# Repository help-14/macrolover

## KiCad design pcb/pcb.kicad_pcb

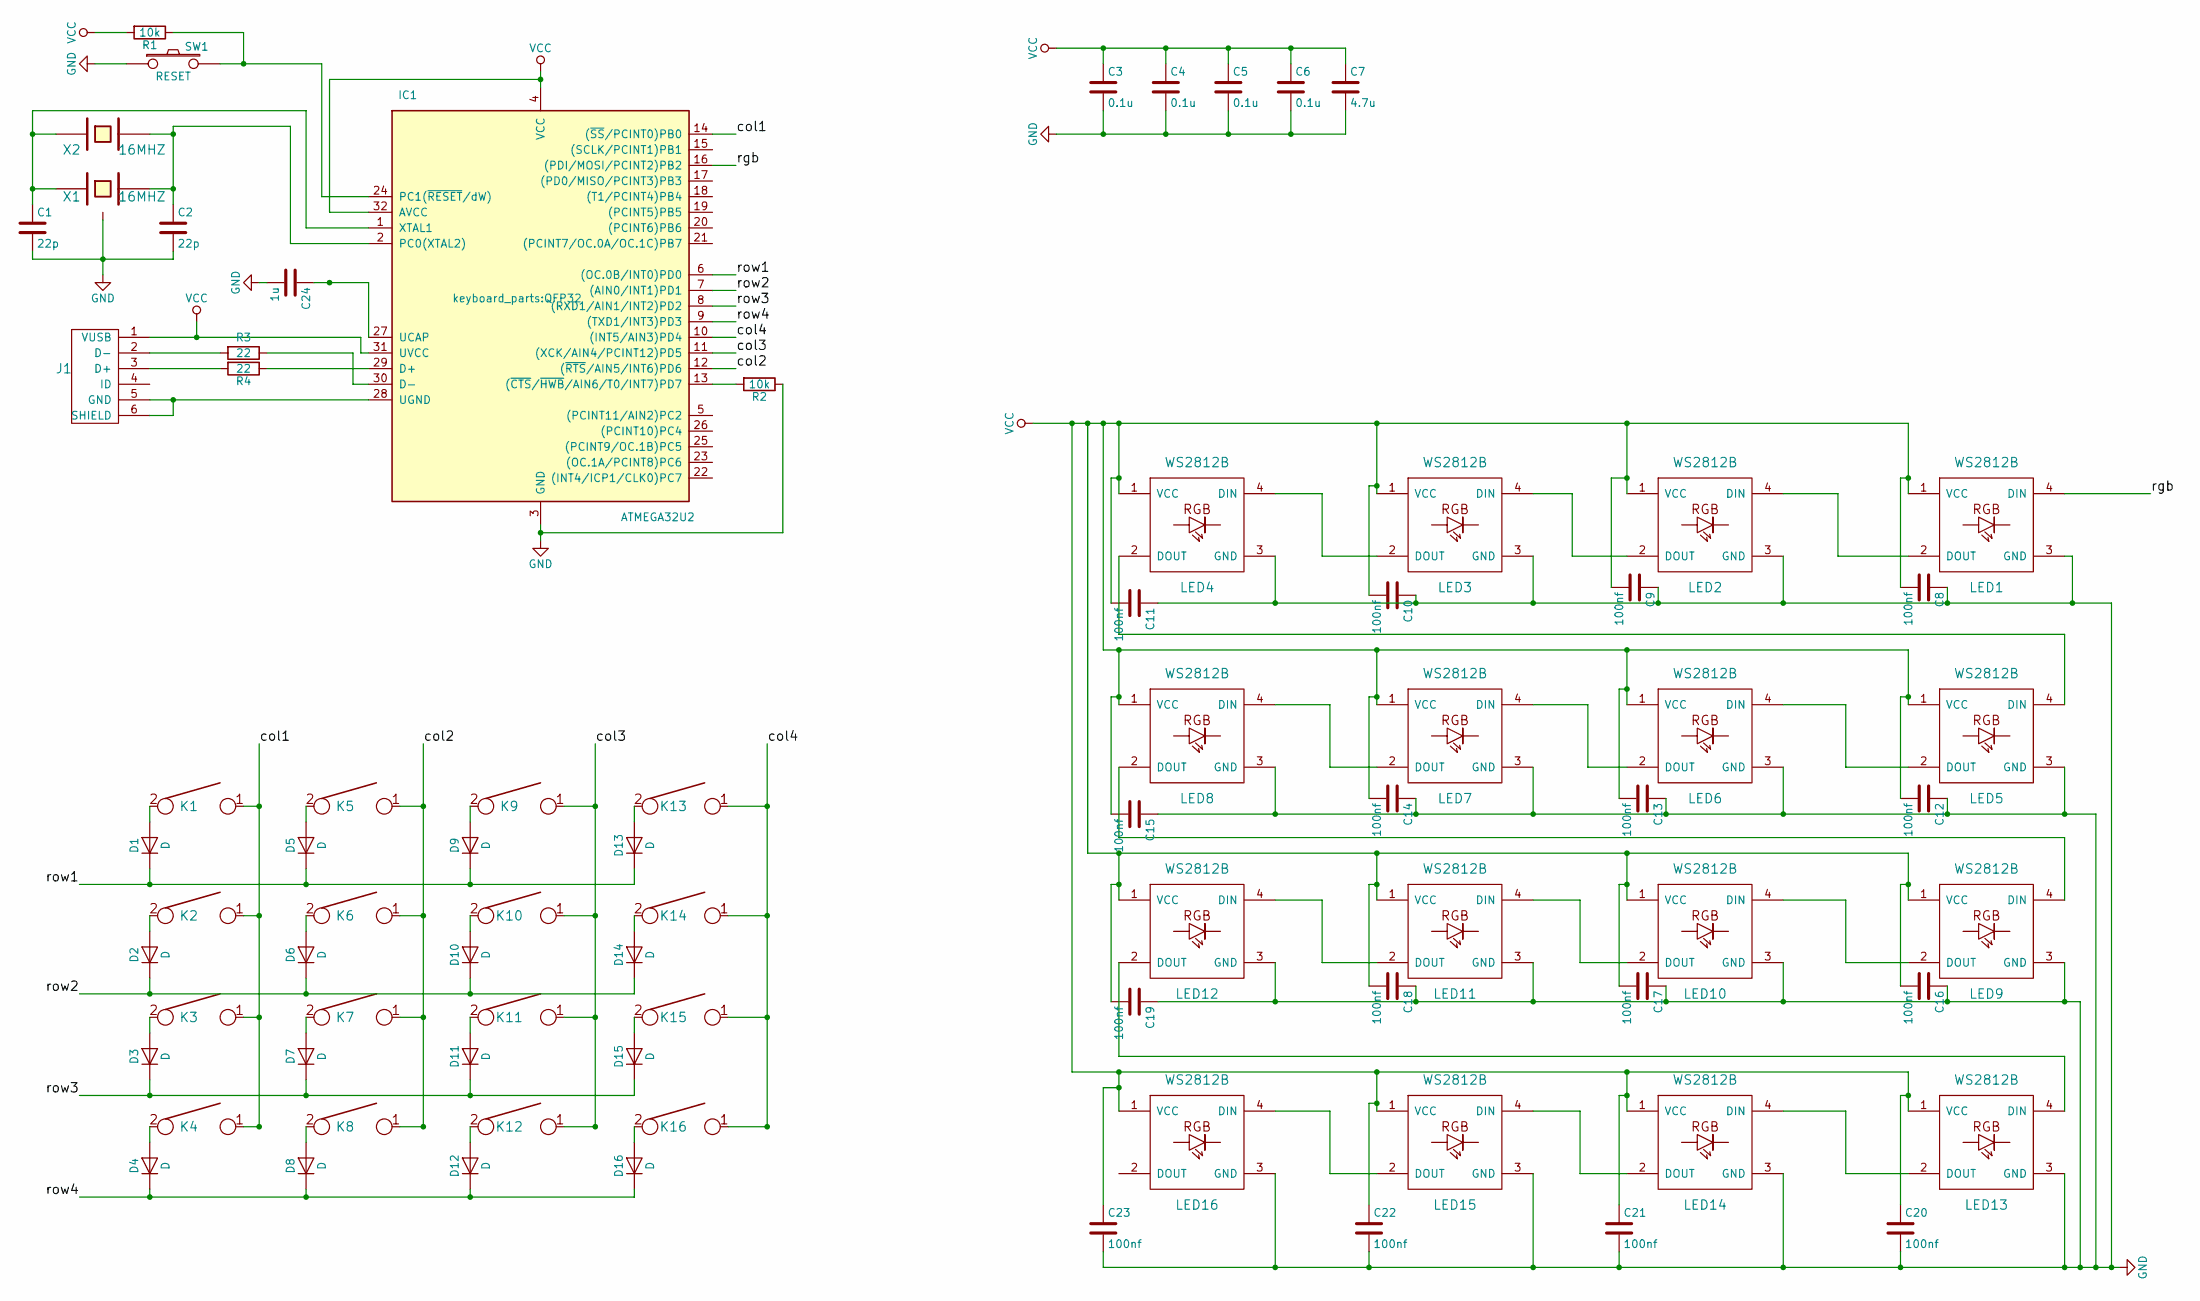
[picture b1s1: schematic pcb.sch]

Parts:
C1, C2: 22p; C_0805
C3, C4, C5, C6: 0.1u; C_0805
C7: 4.7u; C_0805
C8, C9, C10, C11, C12, C13, C14, C15, C16, C17, C18, C19, C20, C21, C22, C23: 100nf; C_0805
C24: 1u; C_0805
D1, D2, D3, D4, D5, D6, D7, D8, D9, D10, D11, D12, D13, D14, D15, D16: D; D_SOD123
IC1: ATMEGA32U2; QFP32
J1: USB_mini_B; USB_miniB_hirose_5S8
K1: 7; Mx_Alps_100
K2: 4; Mx_Alps_100
K3: 1; Mx_Alps_100
K4: 0; Mx_Alps_100
K5: 8; Mx_Alps_100
K6: 5; Mx_Alps_100
K7: 2; Mx_Alps_100
K8: DOT; Mx_Alps_100
K9: 9; Mx_Alps_100
K10: 6; Mx_Alps_100
K11: 3; Mx_Alps_100
K12: EQUAL; Mx_Alps_100
K13: DEVIDE; Mx_Alps_100
K14: *; Mx_Alps_100
K15: -; Mx_Alps_100
K16: +; Mx_Alps_100
LED1, LED2, LED3, LED4, LED5, LED6, LED7, LED8, LED9, LED10, LED11, LED12, LED13, LED14, LED15, LED16: WS2812B
R1, R2: 10k; R_0805
R3, R4: 22; R_0805
SW1: RESET; SW_SPST_TL3342
X1: 16MHZ; Crystal_SMD_SeikoEpson_TSX3225-4pin_3.2x2.5mm
X2: 16MHZ; XTAL_HC_49_TH

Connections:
/col1: IC1.14 ((~SS~/PCINT0)PB0), K1.1, K2.1, K3.1, K4.1
/col2: IC1.12 ((~RTS~/AIN5/INT6)PD6), K5.1, K6.1, K7.1, K8.1
/col3: IC1.11 ((XCK/AIN4/PCINT12)PD5), K9.1, K10.1, K11.1, K12.1
/col4: IC1.10 ((INT5/AIN3)PD4), K13.1, K14.1, K15.1, K16.1
/rgb: IC1.16 ((PDI/MOSI/PCINT2)PB2), LED1.4 (DIN)
/row1: D1.1 (K), D5.1 (K), D9.1 (K), D13.1 (K), IC1.6 ((OC.0B/INT0)PD0)
/row2: D2.1 (K), D6.1 (K), D10.1 (K), D14.1 (K), IC1.7 ((AIN0/INT1)PD1)
/row3: D3.1 (K), D7.1 (K), D11.1 (K), D15.1 (K), IC1.8 ((RXD1/AIN1/INT2)PD2)
/row4: D4.1 (K), D8.1 (K), D12.1 (K), D16.1 (K), IC1.9 ((TXD1/INT3)PD3)
GND: C1.2, C2.2, C3.2, C4.2, C5.2, C6.2, C7.2, C8.1, C9.1, C10.1, C11.1, C12.1, C13.1, C14.1, C15.1, C16.1, C17.1, C18.1, C19.1, C20.2, C21.2, C22.2, C23.2, C24.2, IC1.3 (GND), LED1.3 (GND), LED2.3 (GND), LED3.3 (GND), LED4.3 (GND), LED5.3 (GND), LED6.3 (GND), LED7.3 (GND), LED8.3 (GND), LED9.3 (GND), LED10.3 (GND), LED11.3 (GND), LED12.3 (GND), LED13.3 (GND), LED14.3 (GND), LED15.3 (GND), LED16.3 (GND), R2.1, SW1.1, X1.3
unnamed: C1.1, IC1.1 (XTAL1), X1.1, X2.1
unnamed: C2.1, IC1.2 (PC0(XTAL2)), X1.2, X2.2
unnamed: C24.1, IC1.27 (UCAP)
unnamed: D1.2 (A), K1.2
unnamed: D2.2 (A), K2.2
unnamed: D3.2 (A), K3.2
unnamed: D4.2 (A), K4.2
unnamed: D5.2 (A), K5.2
unnamed: D6.2 (A), K6.2
unnamed: D7.2 (A), K7.2
unnamed: D8.2 (A), K8.2
unnamed: D9.2 (A), K9.2
unnamed: D10.2 (A), K10.2
unnamed: D11.2 (A), K11.2
unnamed: D12.2 (A), K12.2
unnamed: D13.2 (A), K13.2
unnamed: D14.2 (A), K14.2
unnamed: D15.2 (A), K15.2
unnamed: D16.2 (A), K16.2
unnamed: IC1.13 ((~CTS~/~HWB~/AIN6/T0/INT7)PD7), R2.2
unnamed: IC1.24 (PC1(~RESET~/dW)), R1.1, SW1.2
unnamed: IC1.28 (UGND), J1.5 (GND), J1.6 (SHIELD)
unnamed: IC1.29 (D+), R4.1
unnamed: IC1.30 (D-), R3.1
unnamed: J1.2 (D-), R3.2
unnamed: J1.3 (D+), R4.2
unnamed: LED1.2 (DOUT), LED2.4 (DIN)
unnamed: LED2.2 (DOUT), LED3.4 (DIN)
unnamed: LED3.2 (DOUT), LED4.4 (DIN)
unnamed: LED4.2 (DOUT), LED5.4 (DIN)
unnamed: LED5.2 (DOUT), LED6.4 (DIN)
unnamed: LED6.2 (DOUT), LED7.4 (DIN)
unnamed: LED7.2 (DOUT), LED8.4 (DIN)
unnamed: LED8.2 (DOUT), LED9.4 (DIN)
unnamed: LED10.2 (DOUT), LED11.4 (DIN)
unnamed: LED9.2 (DOUT), LED10.4 (DIN)
unnamed: LED11.2 (DOUT), LED12.4 (DIN)
unnamed: LED12.2 (DOUT), LED13.4 (DIN)
unnamed: LED13.2 (DOUT), LED14.4 (DIN)
unnamed: LED14.2 (DOUT), LED15.4 (DIN)
unnamed: LED15.2 (DOUT), LED16.4 (DIN)
VCC: C3.1, C4.1, C5.1, C6.1, C7.1, C8.2, C9.2, C10.2, C11.2, C12.2, C13.2, C14.2, C15.2, C16.2, C17.2, C18.2, C19.2, C20.1, C21.1, C22.1, C23.1, IC1.4 (VCC), IC1.31 (UVCC), IC1.32 (AVCC), J1.1 (VUSB), LED1.1 (VCC), LED2.1 (VCC), LED3.1 (VCC), LED4.1 (VCC), LED5.1 (VCC), LED6.1 (VCC), LED7.1 (VCC), LED8.1 (VCC), LED9.1 (VCC), LED10.1 (VCC), LED11.1 (VCC), LED12.1 (VCC), LED13.1 (VCC), LED14.1 (VCC), LED15.1 (VCC), LED16.1 (VCC), R1.2

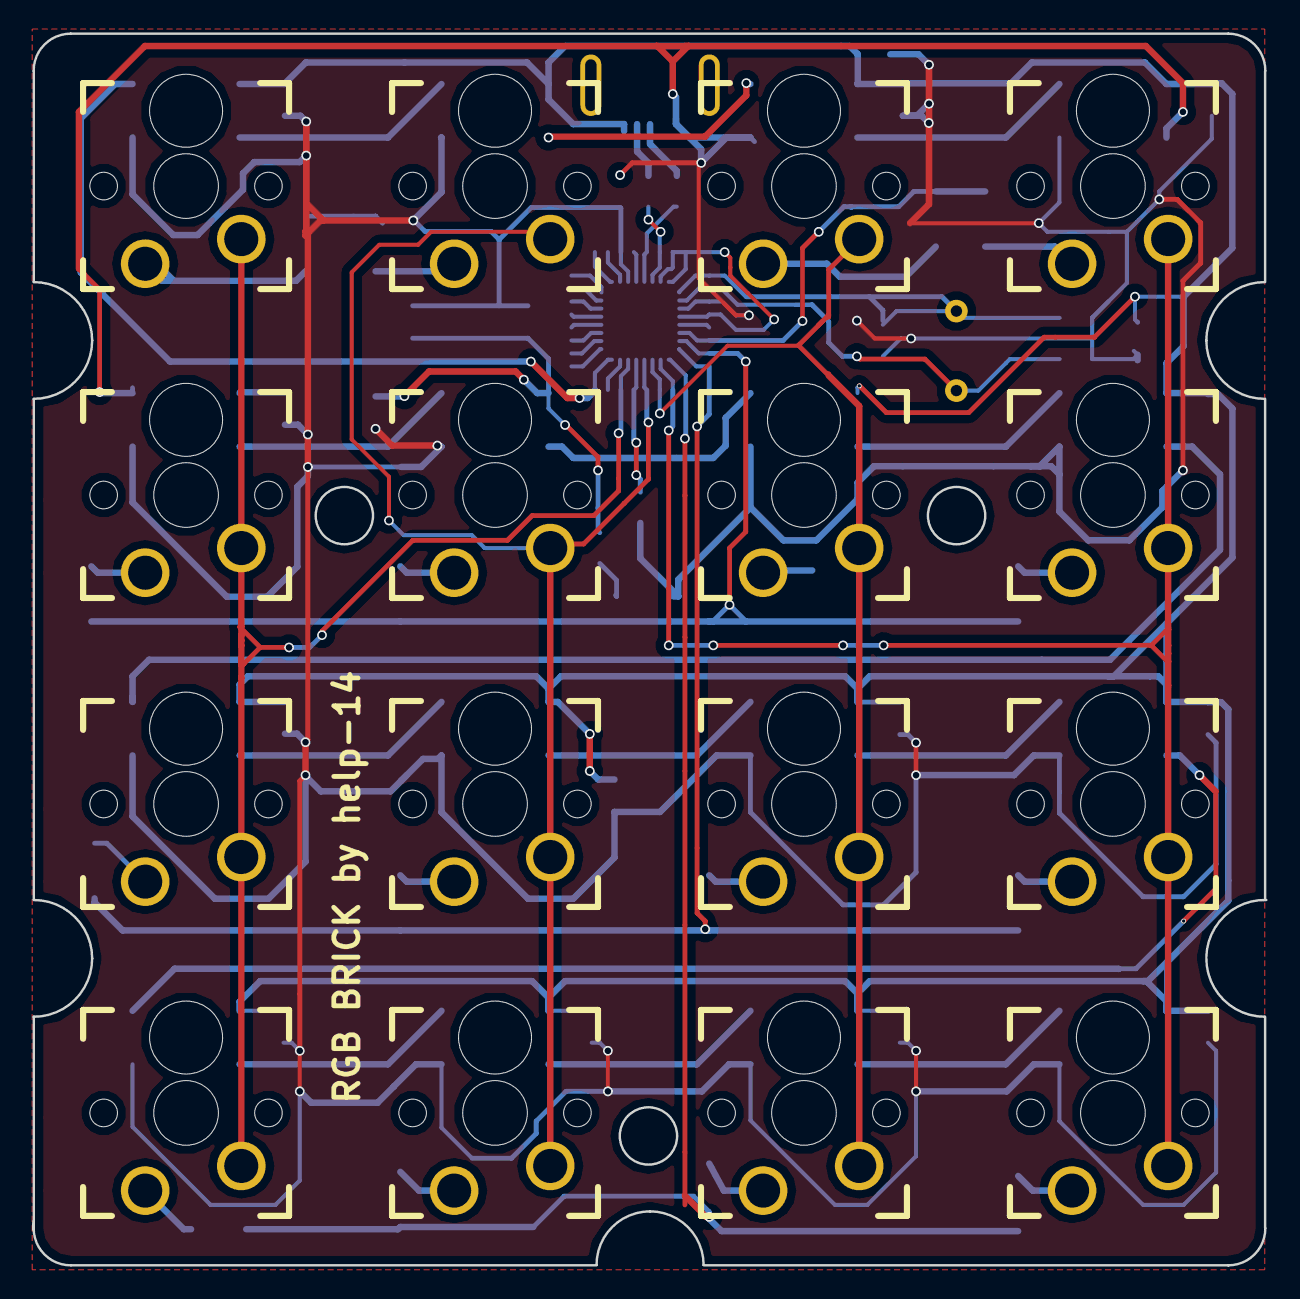
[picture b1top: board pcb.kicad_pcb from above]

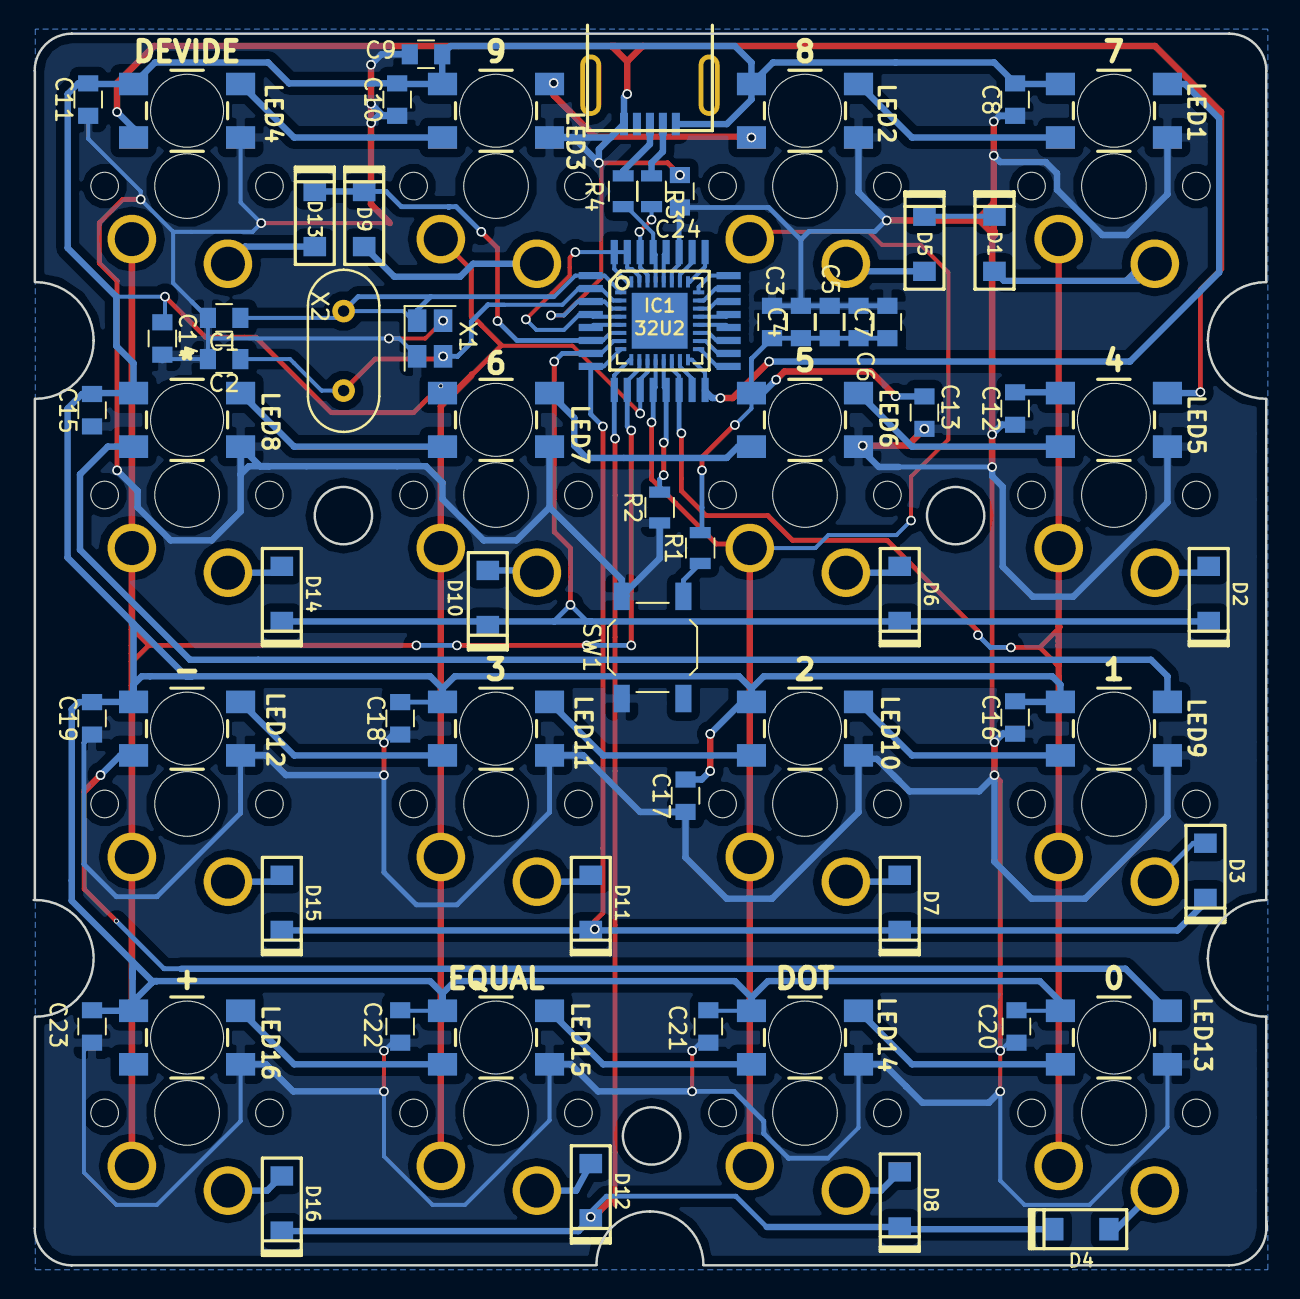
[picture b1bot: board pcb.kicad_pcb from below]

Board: 2 copper layers, 76.0 x 75.9 mm, 82 parts (66 on the bottom side), 52 nets.

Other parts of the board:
U2: QFN-32-1EP_5x5mm_Pitch0.5mm

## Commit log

2017-02-24 create proj
2017-02-26 almost done
2017-02-27 wiring
2017-02-27 update submodule
2017-02-27 Updated submodule mechkey-kicad-lib
2017-02-27 re wiring
2017-02-28 v1 complete
2017-02-28 Removed submodule mechkey-kicad-lib
2017-02-28 re-organize
2017-03-06 change to atmega32u2
2017-03-07 rewiring
2017-03-12 done pcb
2017-05-21 small fix
2017-06-08 add qnf32
